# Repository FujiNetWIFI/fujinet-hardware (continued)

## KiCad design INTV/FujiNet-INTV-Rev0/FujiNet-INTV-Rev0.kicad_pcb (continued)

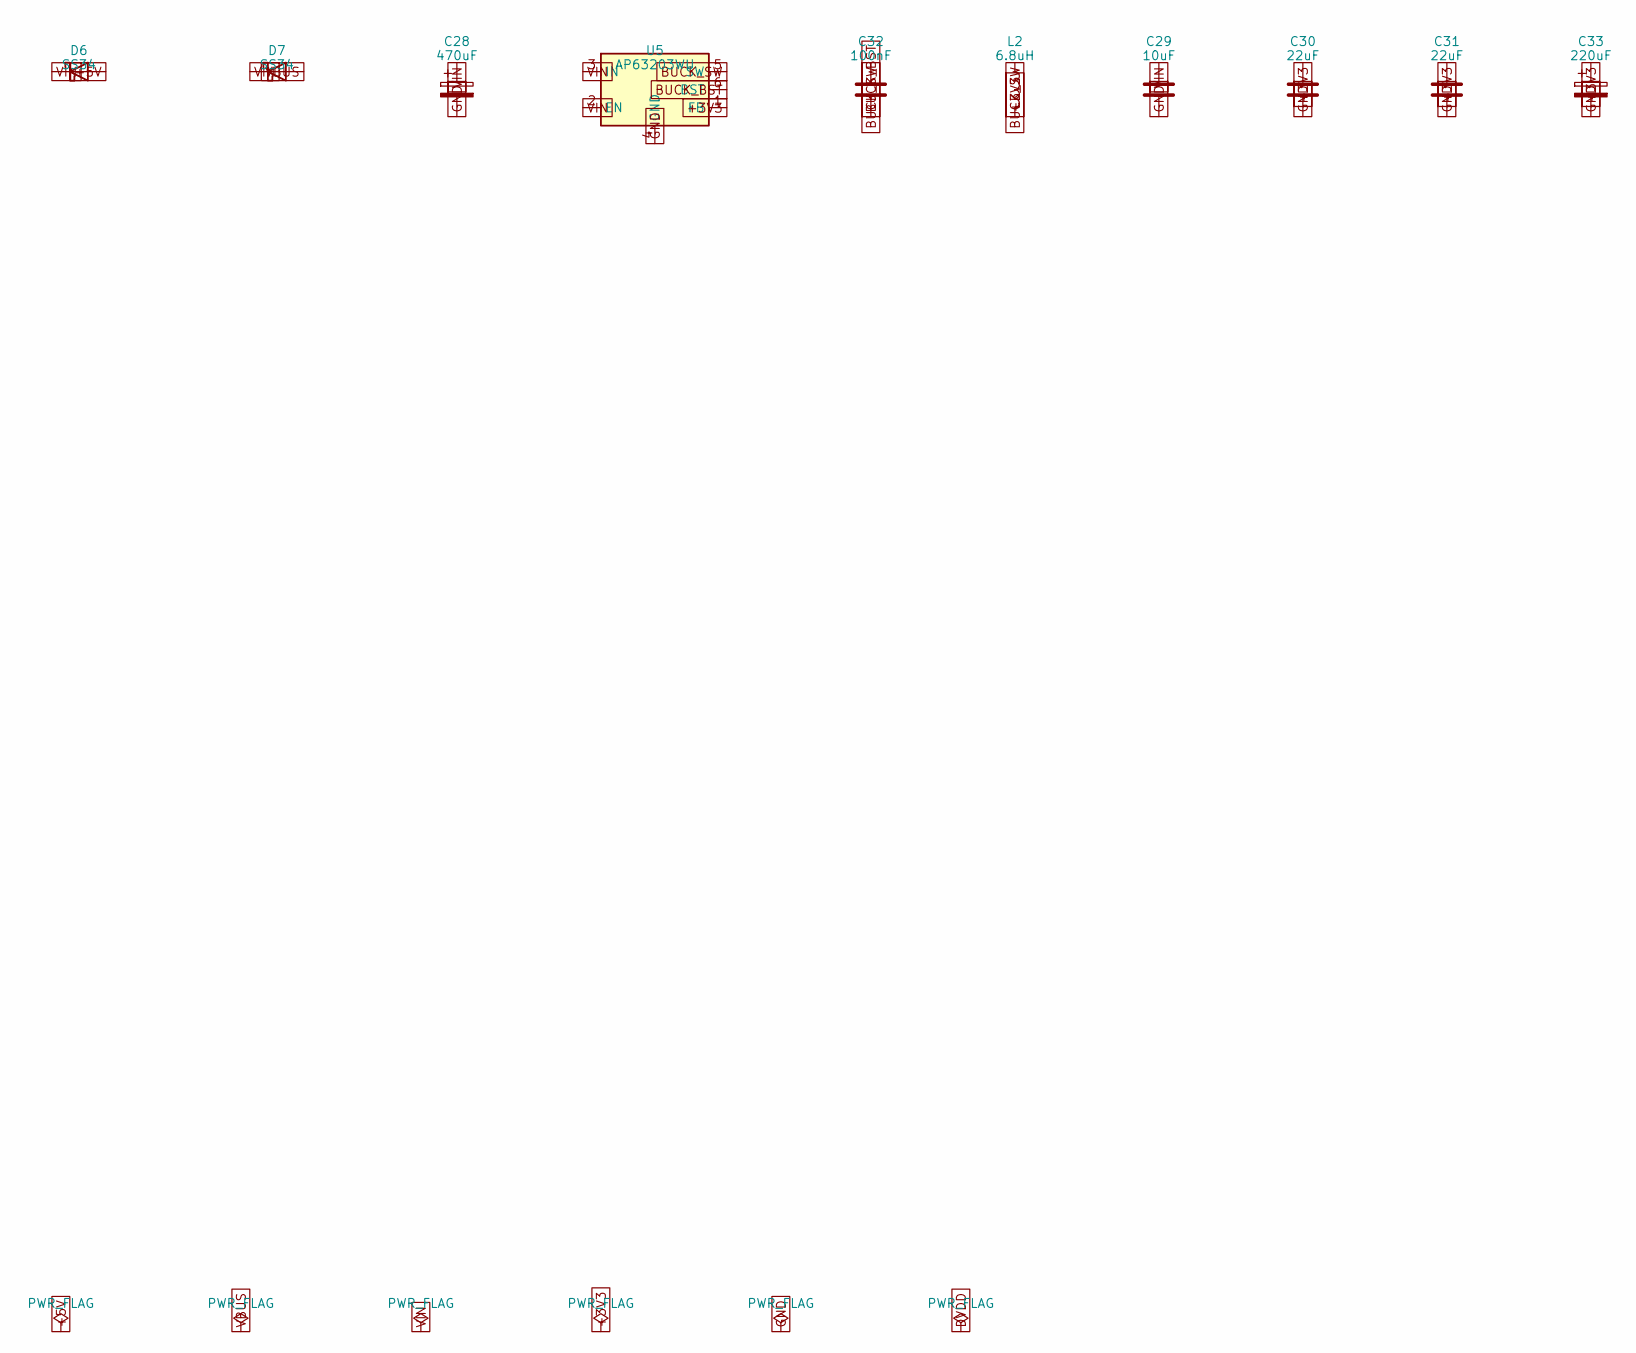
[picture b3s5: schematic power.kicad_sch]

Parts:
C28: 470uF; CP_EIA-7343-31_Kemet-D; MPN 6.3V polymer, 7343
C29: 10uF; C_0805_2012Metric
C30, C31: 22uF; C_0805_2012Metric; LCSC C45783
C32: 100nF; C_0603_1608Metric
C33: 220uF; CP_EIA-7343-31_Kemet-D; MPN 6.3V polymer, 7343
D6, D7: SS34; D_SMA; LCSC C8678
L2: 6.8uH; L_Sunlord_SWPA4030S; MPN 6.8uH >=2.5A shielded 4030
U5: AP63203WU; TSOT-23-6; MPN AP63203WU-7; LCSC C965680

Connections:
+3V3: C30.1, C31.1, C33.1, L2.2, U5.1 (FB); also elsewhere on the board
+5V: D6.2 (A); also elsewhere on the board
BUCK_BST: C32.2, U5.6 (BST)
BUCK_SW: C32.1, L2.1, U5.5 (SW)
GND: C28.2, C29.2, C30.2, C31.2, C33.2, U5.4 (GND); also elsewhere on the board
VBUS: D7.2 (A); also elsewhere on the board
VIN: C28.1, C29.1, D6.1 (K), D7.1 (K), U5.2 (EN), U5.3 (IN); also elsewhere on the board

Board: 4 copper layers, 84 parts (5 on the bottom side), 77 nets, no tracks yet.

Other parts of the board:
H1, H2: MountingHole_5.4mm_NPTH

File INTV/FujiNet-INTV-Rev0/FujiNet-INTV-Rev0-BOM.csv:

"Refs","Value","Footprint","MPN","LCSC","Description","DNP"
"C1,C2","15pF","FujiNet-INTV:C_0603_1608Metric","","","crystal load",""
"C3,C4,C5,C6,C7,C8,C9,C10,C11,C12,C19,C22,C23,C25,C26,C32","100nF","FujiNet-INTV:C_0603_1608Metric","","","IO0 debounce,SD VDD decoupling,U1 decoupling,U2 decoupling,U3 decoupling,WS2812 decoupling,bootstrap",""
"C13,C14,C15,C27","4.7uF","FujiNet-INTV:C_0603_1608Metric","","","DVDD bulk,U3 bulk,VREG_VIN bulk",""
"C16,C17,C20","10uF","FujiNet-INTV:C_0603_1608Metric","","C19702","3V3 bulk near U1,U2 bulk",""
"C18","1uF","FujiNet-INTV:C_0603_1608Metric","","","ECS audio filter (DNP)","DNP"
"C21,C24","1uF","FujiNet-INTV:C_0603_1608Metric","","","EN reset delay,U2 decoupling",""
"C28","470uF","FujiNet-INTV:CP_EIA-7343-31_Kemet-D","6.3V polymer, 7343","","VIN bulk",""
"C29","10uF","FujiNet-INTV:C_0805_2012Metric","","","buck input",""
"C30,C31","22uF","FujiNet-INTV:C_0805_2012Metric","","C45783","buck output",""
"C33","220uF","FujiNet-INTV:CP_EIA-7343-31_Kemet-D","6.3V polymer, 7343","","3V3 bulk (S3 WiFi bursts)",""
"D1","LED","FujiNet-INTV:LED_0603_1608Metric","","","RP activity LED (light pipe)",""
"D2","WS2812B-2020","FujiNet-INTV:LED_WS2812B-2020_PLCC4_2.0x2.0mm","WS2812B-2020","C5149201","status LED (fujiversal LED_STRIP, 1px)",""
"D3,D4,D5","ESD5Z5.0T1G","FujiNet-INTV:D_SOD-523","","C316061","ESD, USB D+,ESD, USB D-,ESD, VBUS",""
"D6,D7","SS34","FujiNet-INTV:D_SMA","","C8678","USB VBUS OR-ing,console 5V OR-ing / backfeed block",""
"J1","INTV_Cart_Edge_44","FujiNet-INTV:INTV_Cart_Edge_44","card edge, 2x22, 2.54mm","","Intellivision cartridge edge (geometry per PiNTY CARD)",""
"J2","microSD","FujiNet-INTV:microSD_SUNTECH_ST-TF-003A","SUNTECH ST-TF-003A","","push-push microSD (footprint per CoCo-FujiNet-Rev0000)",""
"J3","USB-C","FujiNet-INTV:USB_C_Receptacle_HRO_TYPE-C-31-M-12","HRO TYPE-C-31-M-12","C5178539","USB-C 16P (UART/flash port)",""
"L1","3.3uH","FujiNet-INTV:L_2016Metric","AOTA-B201610S3R3-101-T","C42411119","RP2354A core VREG inductor",""
"L2","6.8uH","FujiNet-INTV:L_Sunlord_SWPA4030S","6.8uH >=2.5A shielded 4030","","buck inductor (AP63203 datasheet)",""
"Q1,Q2,Q3","BC847","FujiNet-INTV:SOT-23","","C8598","BOOTSEL force (S3 GPIO5, Hi-Z idle),RUN force (S3 GPIO4, Hi-Z idle),console /RESET open-collector",""
"R1,R4,R8,R9,R10,R11","1k","FujiNet-INTV:R_0603_1608Metric","","","BOOTSEL series,LED series,Q1 base,Q2 base,Q3 base,XOUT series (RP2350 design guide)",""
"R2,R3","27R","FujiNet-INTV:R_0603_1608Metric","","","USB D+ series,USB D- series",""
"R5","1k","FujiNet-INTV:R_0603_1608Metric","","","ECS audio PWM series (DNP)","DNP"
"R6,R7,R13,R18","10k","FujiNet-INTV:R_0603_1608Metric","","","CP2102N /RST pull-up,EN pull-up,QSPI_SS/BOOTSEL pull-up,RUN pull-up",""
"R12","330R","FujiNet-INTV:R_0603_1608Metric","","","WS2812 data series",""
"R14,R15","5.1k","FujiNet-INTV:R_0603_1608Metric","","","CC1 pull-down (UFP),CC2 pull-down (UFP)",""
"R16","22.1k","FujiNet-INTV:R_0603_1608Metric","","","VBUS sense divider hi",""
"R17","47.5k","FujiNet-INTV:R_0603_1608Metric","","","VBUS sense divider lo",""
"RN1","4x10k","FujiNet-INTV:R_Array_Convex_4x0603","","","SD pull-ups",""
"SW1","RUN","FujiNet-INTV:SW_SPST_TL3342","","","RP2354A reset button",""
"SW2","BOOTSEL","FujiNet-INTV:SW_SPST_TL3342","","","RP2354A BOOTSEL button",""
"SW3","RESET","FujiNet-INTV:SW_SPST_TL3342","","","ESP32 reset button",""
"SW4","BOOT","FujiNet-INTV:SW_SPST_TL3342","","","ESP32 IO0 boot button",""
"U1","RP2354A","FujiNet-INTV:QFN-60-1EP_7x7mm_P0.4mm_EP3.4x3.4mm","RP2354A","C41378174","RP2350A + 2MB stacked QSPI flash, QFN-60",""
"U2","ESP32-S3-WROOM-1-N16R8","FujiNet-INTV:ESP32-S3-WROOM-1","ESP32-S3-WROOM-1-N16R8","C2913202","16MB QIO flash / 8MB octal PSRAM (IO35-37 NC)",""
"U3","CP2102N-A02-GQFN28","FujiNet-INTV:QFN-28-1EP_5x5mm_P0.5mm_EP3.35x3.35mm","CP2102N-A02-GQFN28R","","USB-UART bridge (DevKitC-1 UART port)",""
"U4","UMH3N","FujiNet-INTV:SOT-363_SC-70-6","","C123008","auto-program: DTR/RTS -> EN/IO0 (DevKitC-1 circuit)",""
"U5","AP63203WU","FujiNet-INTV:TSOT-23-6","AP63203WU-7","C965680","3.3V/2A sync buck (FB tied to VOUT: fixed 3.3V version)",""
"Y1","12MHz","FujiNet-INTV:Crystal_SMD_3225-4Pin_3.2x2.5mm","ABM8-272-T3","C20625731","12MHz 3225, CL=10pF (per PiNTY)",""

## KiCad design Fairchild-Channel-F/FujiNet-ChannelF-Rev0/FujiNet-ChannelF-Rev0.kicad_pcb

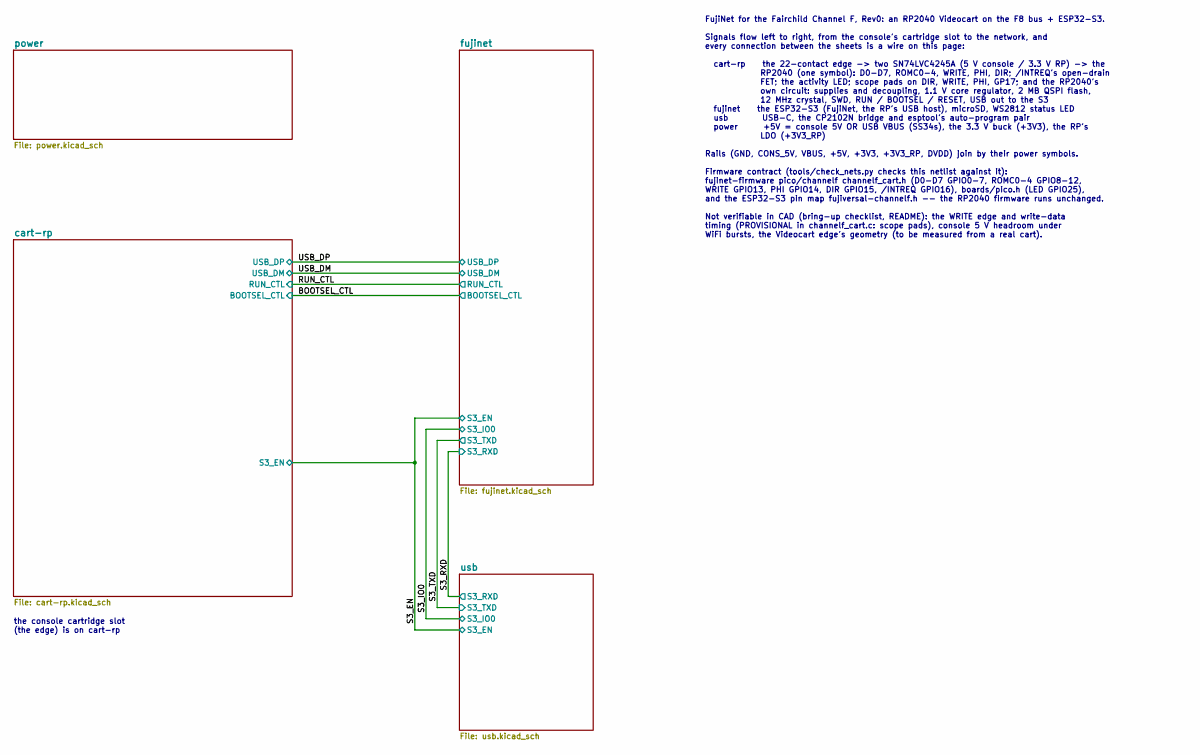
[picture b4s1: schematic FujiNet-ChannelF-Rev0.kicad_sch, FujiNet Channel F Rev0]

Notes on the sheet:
the console cartridge slot (the edge) is on cart-rp
FujiNet for the Fairchild Channel F, Rev0: an RP2040 Videocart on the F8 bus + ESP32-S3. Signals flow left to right, from the console's cartridge slot to the network, and every connection between the sheets is a wire on this page: cart-rp the 22-contact edge -> two SN74LVC4245A (5 V console / 3.3 V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

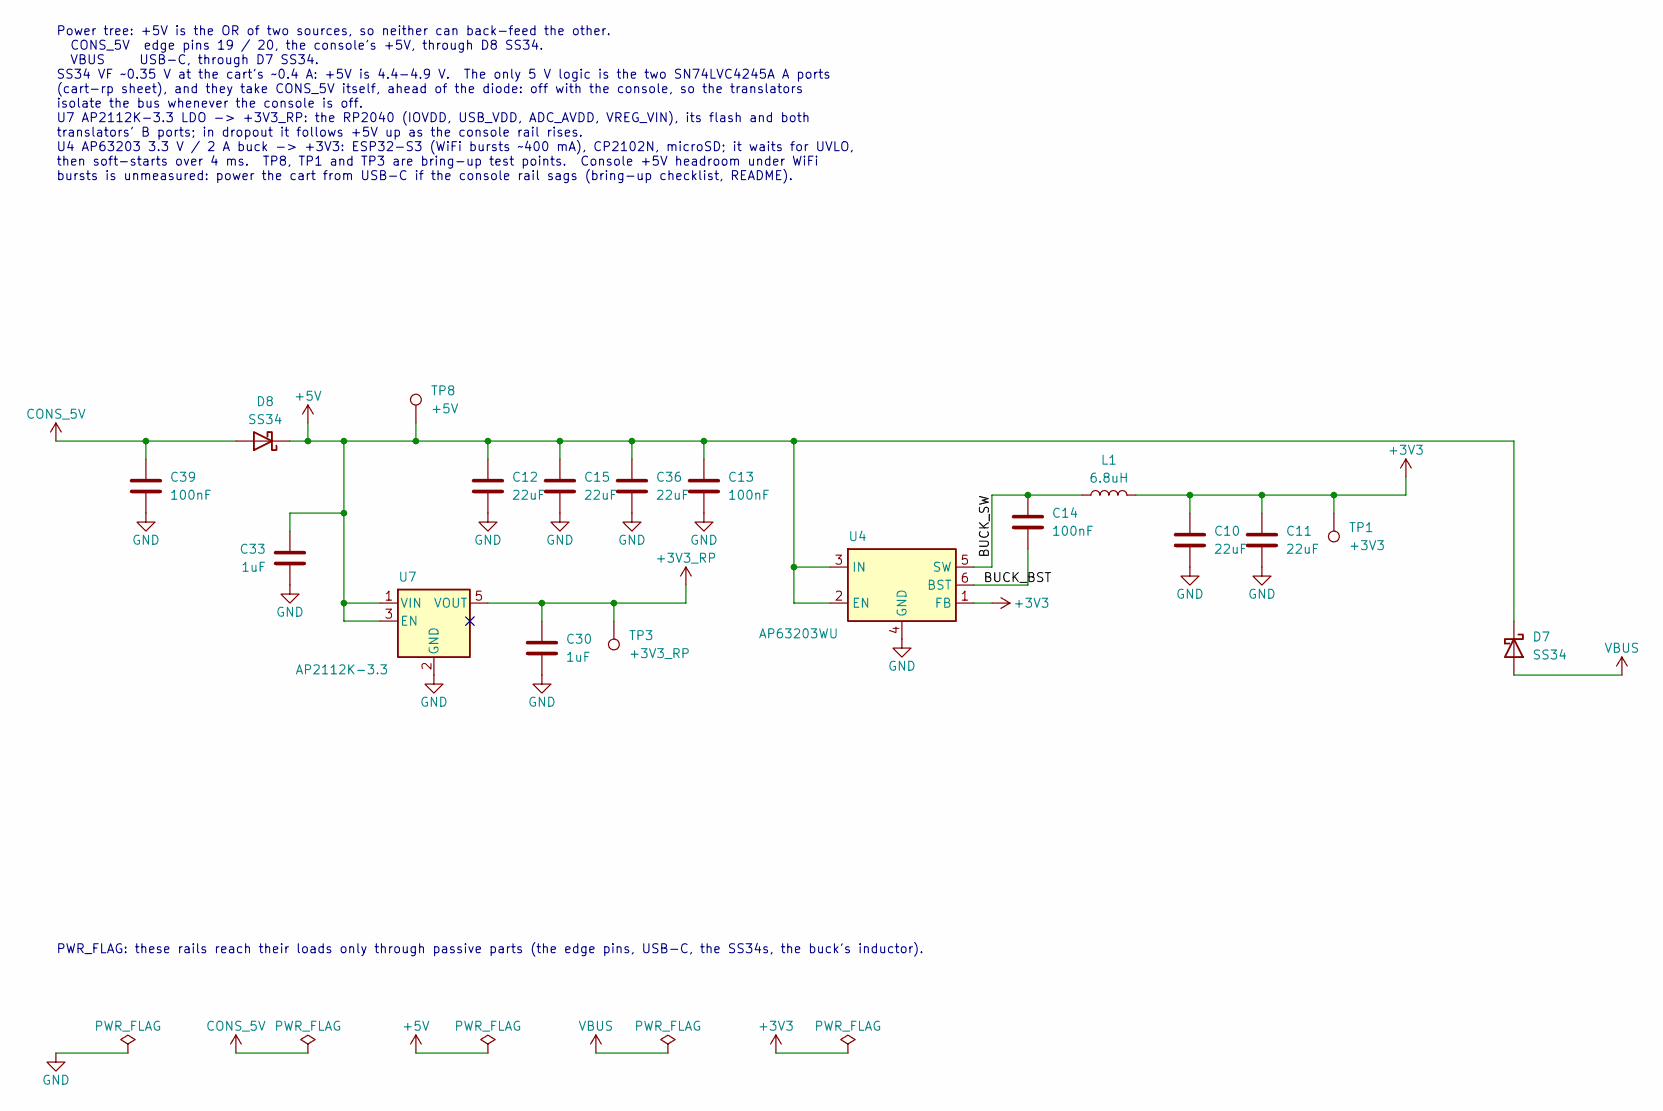
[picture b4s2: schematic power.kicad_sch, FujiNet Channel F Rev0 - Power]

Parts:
C10, C11, C12, C15, C36: 22uF; C_0805_2012Metric; MPN CL21A226MAQNNNE; LCSC C45783
C13, C14, C39: 100nF; C_0603_1608Metric; MPN CC0603KRX7R9BB104; LCSC C14663
C30, C33: 1uF; C_0603_1608Metric; MPN CL10A105KB8NNNC; LCSC C15849
D7, D8: SS34; D_SMA; MPN SS34; LCSC C8678
L1: 6.8uH; L_Sunlord_SWPA4030S; MPN SWPA4030S6R8MT; LCSC C62684
TP1: +3V3; TestPoint_Pad_D1.5mm
TP3: +3V3_RP; TestPoint_Pad_D1.5mm
TP8: +5V; TestPoint_Pad_D1.5mm
U4: AP63203WU; TSOT-23-6; MPN AP63203WU-7; LCSC C780769
U7: AP2112K-3.3; SOT-23-5; MPN AP2112K-3.3TRG1; LCSC C51118

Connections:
+3V3: C10.1, C11.1, L1.2, TP1.1, U4.1 (FB); also elsewhere on the board
+3V3_RP: C30.1, TP3.1, U7.5 (VOUT); also elsewhere on the board
+5V: C12.1, C13.1, C15.1, C33.1, C36.1, D7.1 (K), D8.1 (K), TP8.1, U4.2 (EN), U4.3 (IN), U7.1 (VIN), U7.3 (EN); also elsewhere on the board
/power/BUCK_BST: C14.2, U4.6 (BST)
/power/BUCK_SW: C14.1, L1.1, U4.5 (SW)
CONS_5V: C39.1, D8.2 (A); also elsewhere on the board
GND: C10.2, C11.2, C12.2, C13.2, C15.2, C30.2, C33.2, C36.2, C39.2, U4.4 (GND), U7.2 (GND); also elsewhere on the board
VBUS: D7.2 (A); also elsewhere on the board

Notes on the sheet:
PWR_FLAG: these rails reach their loads only through passive parts (the edge pins, USB-C, the SS34s, the buck's inductor).
Power tree: +5V is the OR of two sources, so neither can back-feed the other. CONS_5V edge pins 19 / 20, the console's +5V, through D8 SS34. VBUS USB-C, through D7 SS34. SS34 VF ~0.35 V at the cart's ~0.4 A: +5V is 4.4-4.9 V. The only 5 V logic is the two SN74LVC4245A A ports (cart-rp sheet), and t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

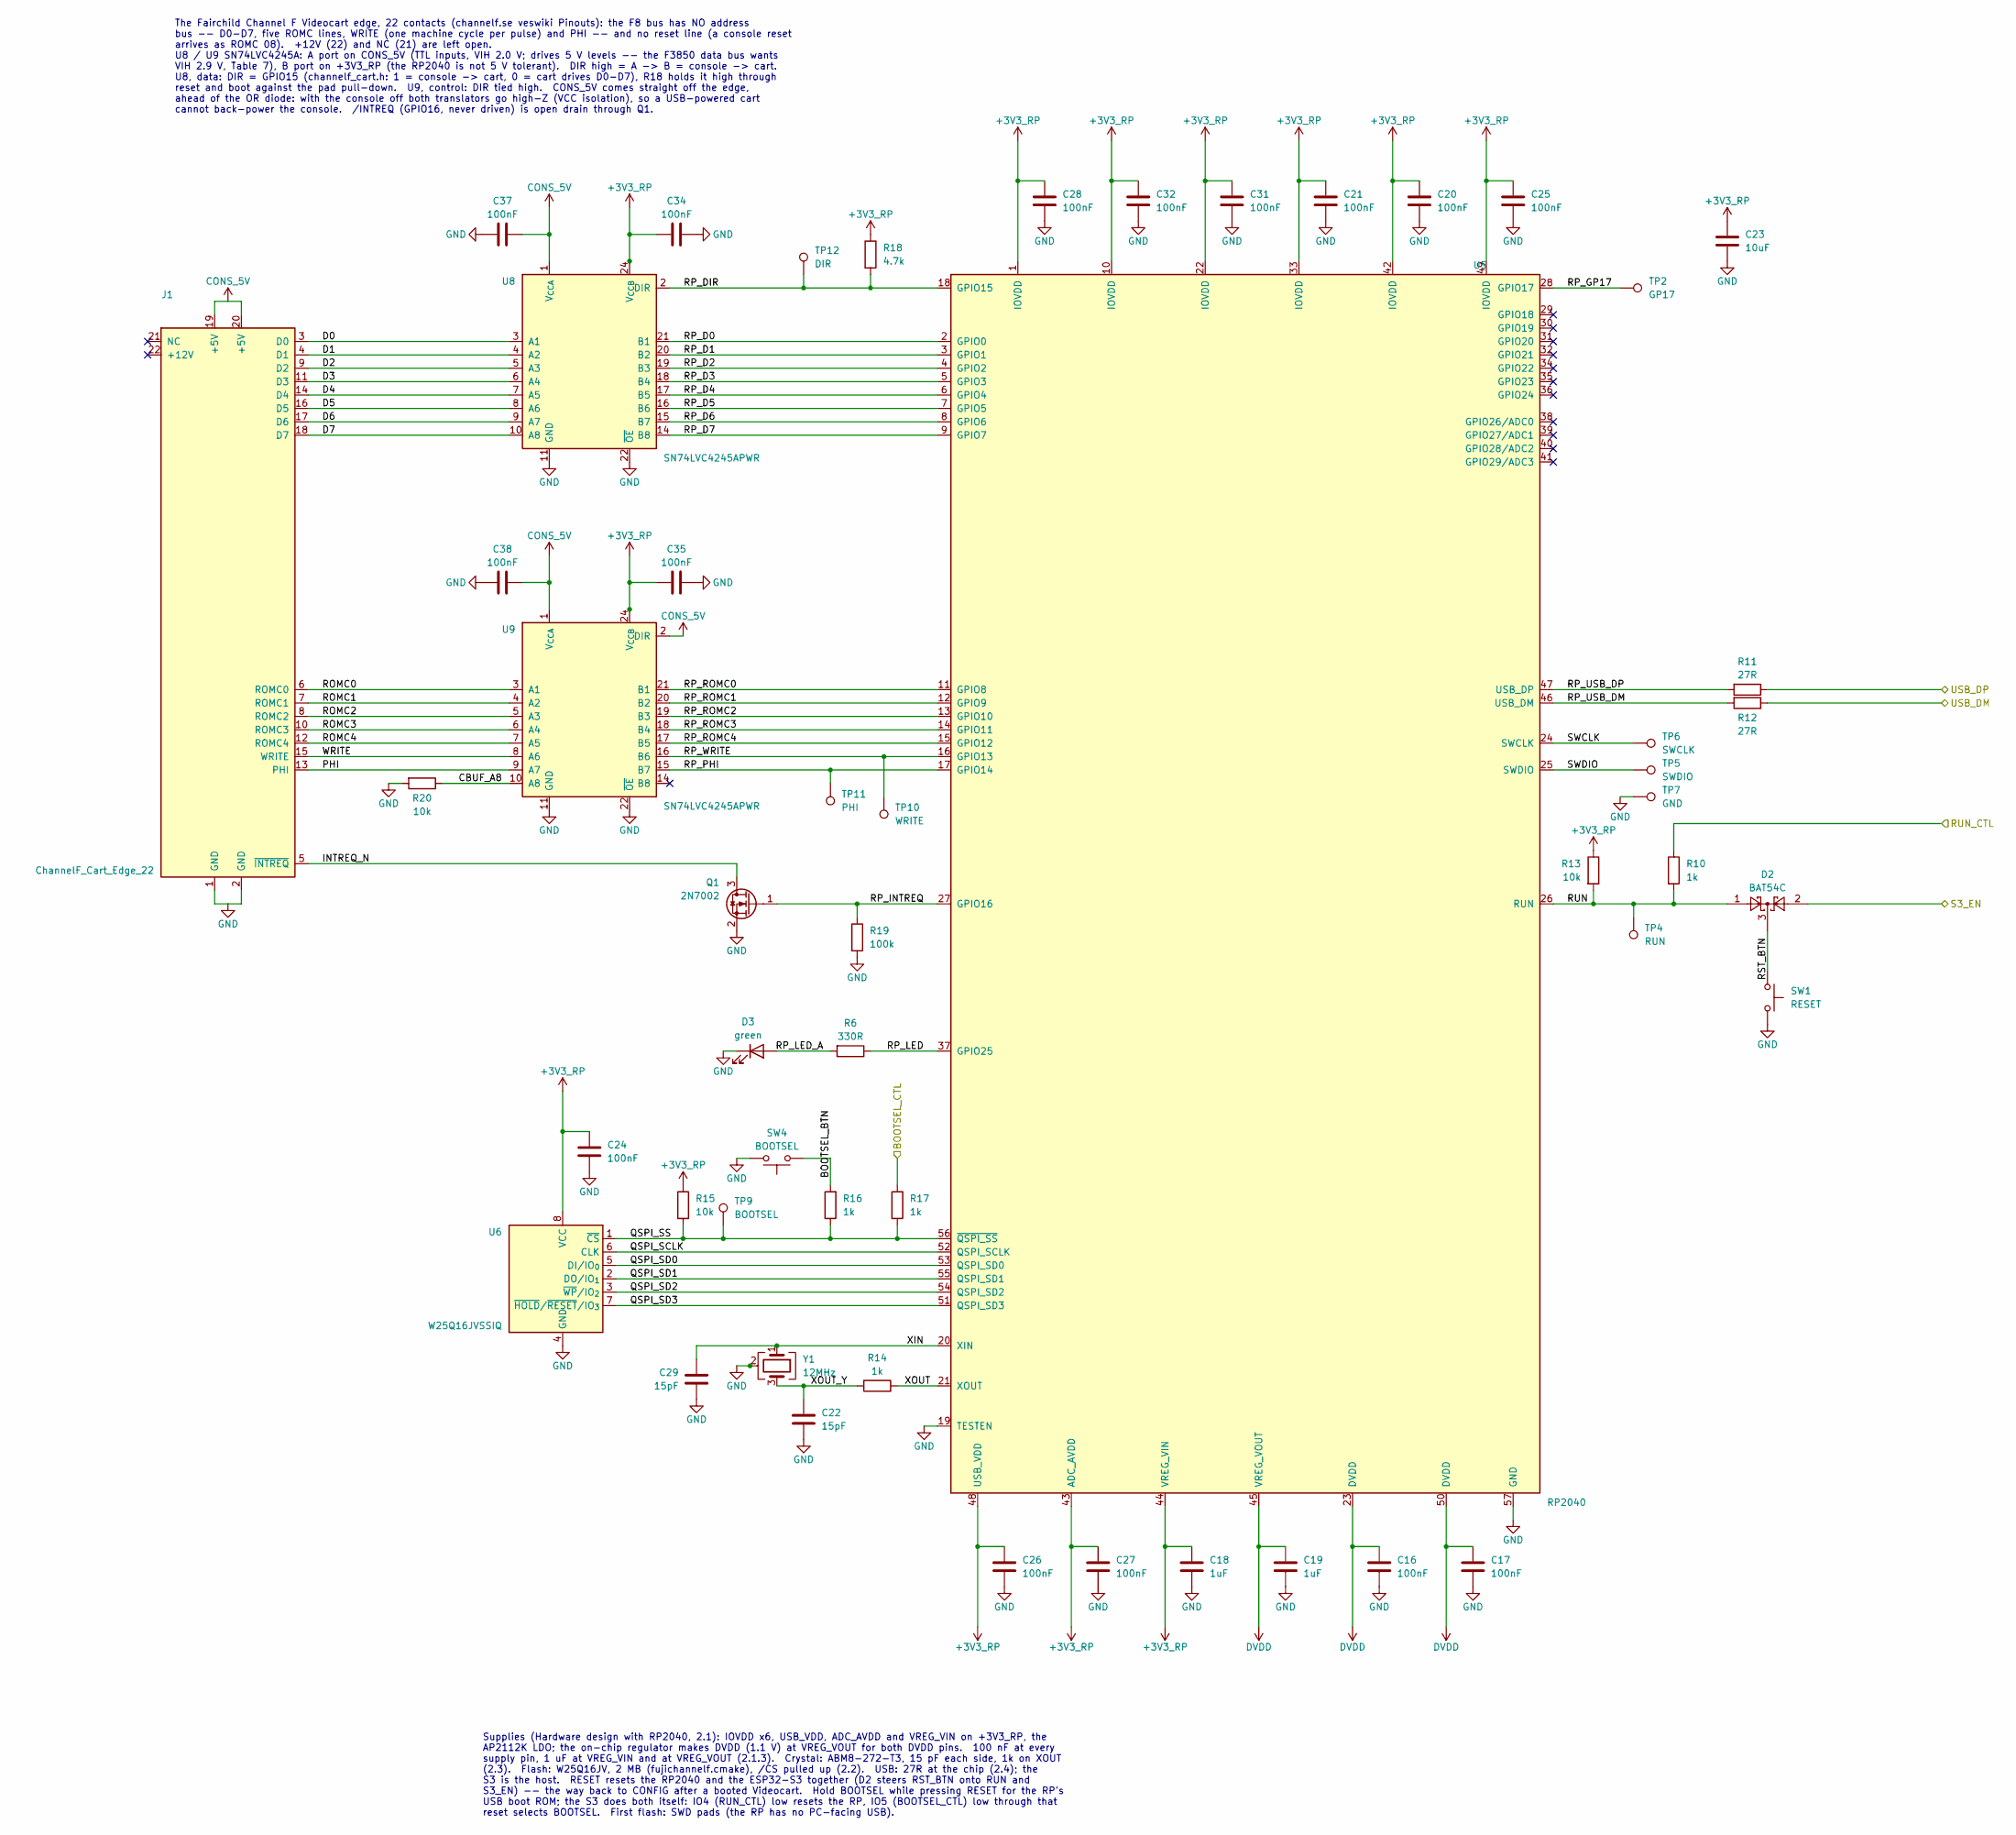
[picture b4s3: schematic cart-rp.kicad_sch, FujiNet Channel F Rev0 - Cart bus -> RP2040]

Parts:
C16, C17, C20, C21, C24, C25, C26, C27, C28, C31, C32, C34, C35, C37, C38: 100nF; C_0603_1608Metric; MPN CC0603KRX7R9BB104; LCSC C14663
C18, C19: 1uF; C_0603_1608Metric; MPN CL10A105KB8NNNC; LCSC C15849
C22, C29: 15pF; C_0603_1608Metric; MPN CL10C150JB8NNNC; LCSC C1644
C23: 10uF; C_0603_1608Metric; MPN CL10A106KP8NNNC; LCSC C19702
D2: BAT54C; SOT-23; MPN BAT54C,215; LCSC C37704
D3: green; LED_0603_1608Metric; MPN KT-0603G; LCSC C12624
J1: ChannelF_Cart_Edge_22; ChannelF_Videocart_Edge_22
Q1: 2N7002; SOT-23; MPN 2N7002; LCSC C8545
R6: 330R; R_0603_1608Metric; MPN 0603WAF3300T5E; LCSC C23138
R10, R14, R16, R17: 1k; R_0603_1608Metric; MPN 0603WAF1001T5E; LCSC C21190
R11, R12: 27R; R_0603_1608Metric; MPN 0603WAF270JT5E; LCSC C25190
R13, R15, R20: 10k; R_0603_1608Metric; MPN 0603WAF1002T5E; LCSC C25804
R18: 4.7k; R_0603_1608Metric; MPN 0603WAF4701T5E; LCSC C23162
R19: 100k; R_0603_1608Metric; MPN 0603WAF1003T5E; LCSC C25803
SW1: RESET; SW_SPST_TL3342; MPN TL3342F160QG; LCSC C2886898
SW4: BOOTSEL; SW_SPST_TL3342; MPN TL3342F160QG; LCSC C2886898
TP2: GP17; TestPoint_Pad_D1.5mm
TP4: RUN; TestPoint_Pad_D1.5mm
TP5: SWDIO; TestPoint_Pad_D1.5mm
TP6: SWCLK; TestPoint_Pad_D1.5mm
TP7: GND; TestPoint_Pad_D1.5mm
TP9: BOOTSEL; TestPoint_Pad_D1.5mm
TP10: WRITE; TestPoint_Pad_D1.5mm
TP11: PHI; TestPoint_Pad_D1.5mm
TP12: DIR; TestPoint_Pad_D1.5mm
U5: RP2040; QFN-56-1EP_7x7mm_P0.4mm_EP3.2x3.2mm; MPN RP2040; LCSC C2040
U6: W25Q16JVSSIQ; SOIC-8_5.3x5.3mm_P1.27mm; MPN W25Q16JVSSIQ; LCSC C82317
U8, U9: SN74LVC4245APWR; TSSOP-24_4.4x7.8mm_P0.65mm; MPN SN74LVC4245APWR; LCSC C7859
Y1: 12MHz; Crystal_SMD_3225-4Pin_3.2x2.5mm; MPN ABM8-272-T3; LCSC C20625731

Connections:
+3V3_RP: C18.1, C20.1, C21.1, C23.1, C24.1, C25.1, C26.1, C27.1, C28.1, C31.1, C32.1, C34.1, C35.1, R13.1, R15.1, R18.1, U5.1 (IOVDD), U5.10 (IOVDD), U5.22 (IOVDD), U5.33 (IOVDD), U5.42 (IOVDD), U5.43 (ADC_AVDD), U5.44 (VREG_VIN), U5.48 (USB_VDD), U5.49 (IOVDD), U6.8 (VCC), U8.23 (V_{CCB}), U8.24 (V_{CCB}), U9.23 (V_{CCB}), U9.24 (V_{CCB}); also elsewhere on the board
/BOOTSEL_CTL: R17.1; also elsewhere on the board
/RUN_CTL: R10.1; also elsewhere on the board
/S3_EN: D2.2; also elsewhere on the board
/USB_DM: R12.1; also elsewhere on the board
/USB_DP: R11.1; also elsewhere on the board
/cart-rp/BOOTSEL_BTN: R16.2, SW4.1
/cart-rp/CBUF_A8: R20.1, U9.10 (A8)
/cart-rp/D0: J1.3 (D0), U8.3 (A1)
/cart-rp/D1: J1.4 (D1), U8.4 (A2)
/cart-rp/D2: J1.9 (D2), U8.5 (A3)
/cart-rp/D3: J1.11 (D3), U8.6 (A4)
/cart-rp/D4: J1.14 (D4), U8.7 (A5)
/cart-rp/D5: J1.16 (D5), U8.8 (A6)
/cart-rp/D6: J1.17 (D6), U8.9 (A7)
/cart-rp/D7: J1.18 (D7), U8.10 (A8)
/cart-rp/INTREQ_N: J1.5 (~INTREQ), Q1.3 (D)
/cart-rp/PHI: J1.13 (PHI), U9.9 (A7)
/cart-rp/QSPI_SCLK: U5.52 (QSPI_SCLK), U6.6 (CLK)
/cart-rp/QSPI_SD0: U5.53 (QSPI_SD0), U6.5 (DI/IO_{0})
/cart-rp/QSPI_SD1: U5.55 (QSPI_SD1), U6.2 (DO/IO_{1})
/cart-rp/QSPI_SD2: U5.54 (QSPI_SD2), U6.3 (~WP/IO_{2})
/cart-rp/QSPI_SD3: U5.51 (QSPI_SD3), U6.7 (~HOLD/~RESET/IO_{3})
/cart-rp/QSPI_SS: R15.2, R16.1, R17.2, TP9.1, U5.56 (~QSPI_SS), U6.1 (~CS)
/cart-rp/ROMC0: J1.6 (ROMC0), U9.3 (A1)
/cart-rp/ROMC1: J1.7 (ROMC1), U9.4 (A2)
/cart-rp/ROMC2: J1.8 (ROMC2), U9.5 (A3)
/cart-rp/ROMC3: J1.10 (ROMC3), U9.6 (A4)
/cart-rp/ROMC4: J1.12 (ROMC4), U9.7 (A5)
/cart-rp/RP_D0: U5.2 (GPIO0), U8.21 (B1)
/cart-rp/RP_D1: U5.3 (GPIO1), U8.20 (B2)
/cart-rp/RP_D2: U5.4 (GPIO2), U8.19 (B3)
/cart-rp/RP_D3: U5.5 (GPIO3), U8.18 (B4)
/cart-rp/RP_D4: U5.6 (GPIO4), U8.17 (B5)
/cart-rp/RP_D5: U5.7 (GPIO5), U8.16 (B6)
/cart-rp/RP_D6: U5.8 (GPIO6), U8.15 (B7)
/cart-rp/RP_D7: U5.9 (GPIO7), U8.14 (B8)
/cart-rp/RP_DIR: R18.2, TP12.1, U5.18 (GPIO15), U8.2 (DIR)
/cart-rp/RP_GP17: TP2.1, U5.28 (GPIO17)
/cart-rp/RP_INTREQ: Q1.1 (G), R19.1, U5.27 (GPIO16)
/cart-rp/RP_LED: R6.1, U5.37 (GPIO25)
/cart-rp/RP_LED_A: D3.2 (A), R6.2
/cart-rp/RP_PHI: TP11.1, U5.17 (GPIO14), U9.15 (B7)
/cart-rp/RP_ROMC0: U5.11 (GPIO8), U9.21 (B1)
/cart-rp/RP_ROMC1: U5.12 (GPIO9), U9.20 (B2)
/cart-rp/RP_ROMC2: U5.13 (GPIO10), U9.19 (B3)
/cart-rp/RP_ROMC3: U5.14 (GPIO11), U9.18 (B4)
/cart-rp/RP_ROMC4: U5.15 (GPIO12), U9.17 (B5)
/cart-rp/RP_USB_DM: R12.2, U5.46 (USB_DM)
/cart-rp/RP_USB_DP: R11.2, U5.47 (USB_DP)
/cart-rp/RP_WRITE: TP10.1, U5.16 (GPIO13), U9.16 (B6)
/cart-rp/RST_BTN: D2.3, SW1.1
/cart-rp/RUN: D2.1, R10.2, R13.2, TP4.1, U5.26 (RUN)
/cart-rp/SWCLK: TP6.1, U5.24 (SWCLK)
/cart-rp/SWDIO: TP5.1, U5.25 (SWDIO)
/cart-rp/WRITE: J1.15 (WRITE), U9.8 (A6)
/cart-rp/XIN: C29.1, U5.20 (XIN), Y1.1
/cart-rp/XOUT: R14.1, U5.21 (XOUT)
/cart-rp/XOUT_Y: C22.1, R14.2, Y1.3
CONS_5V: C37.1, C38.1, J1.19 (+5V), J1.20 (+5V), U8.1 (V_{CCA}), U9.1 (V_{CCA}), U9.2 (DIR); also elsewhere on the board
DVDD: C16.1, C17.1, C19.1, U5.23 (DVDD), U5.45 (VREG_VOUT), U5.50 (DVDD)
GND: C16.2, C17.2, C18.2, C19.2, C20.2, C21.2, C22.2, C23.2, C24.2, C25.2, C26.2, C27.2, C28.2, C29.2, C31.2, C32.2, C34.2, C35.2, C37.2, C38.2, D3.1 (K), J1.1 (GND), J1.2 (GND), Q1.2 (S), R19.2, R20.2, SW1.2, SW4.2, TP7.1, U5.19 (TESTEN), U5.57 (GND), U6.4 (GND), U8.11 (GND), U8.12 (GND), U8.13 (GND), U8.22 (~OE), U9.11 (GND), U9.12 (GND), U9.13 (GND), U9.22 (~OE), Y1.2 (G), Y1.4 (G); also elsewhere on the board

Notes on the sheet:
The Fairchild Channel F Videocart edge, 22 contacts (channelf.se veswiki Pinouts): the F8 bus has NO address bus -- D0-D7, five ROMC lines, WRITE (one machine cycle per pulse) and PHI -- and no reset line (a console reset arrives as ROMC 08). +12V (22) and NC (21) are left open. U8 / U9 SN74LVC4245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
Supplies (Hardware design with RP2040, 2.1): IOVDD x6, USB_VDD, ADC_AVDD and VREG_VIN on +3V3_RP, the AP2112K LDO; the on-chip regulator makes DVDD (1.1 V) at VREG_VOUT for both DVDD pins. 100 nF at every supply pin, 1 uF at VREG_VIN and at VREG_VOUT (2.1.3). Crystal: ABM8-272-T3, 15 pF each side, 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

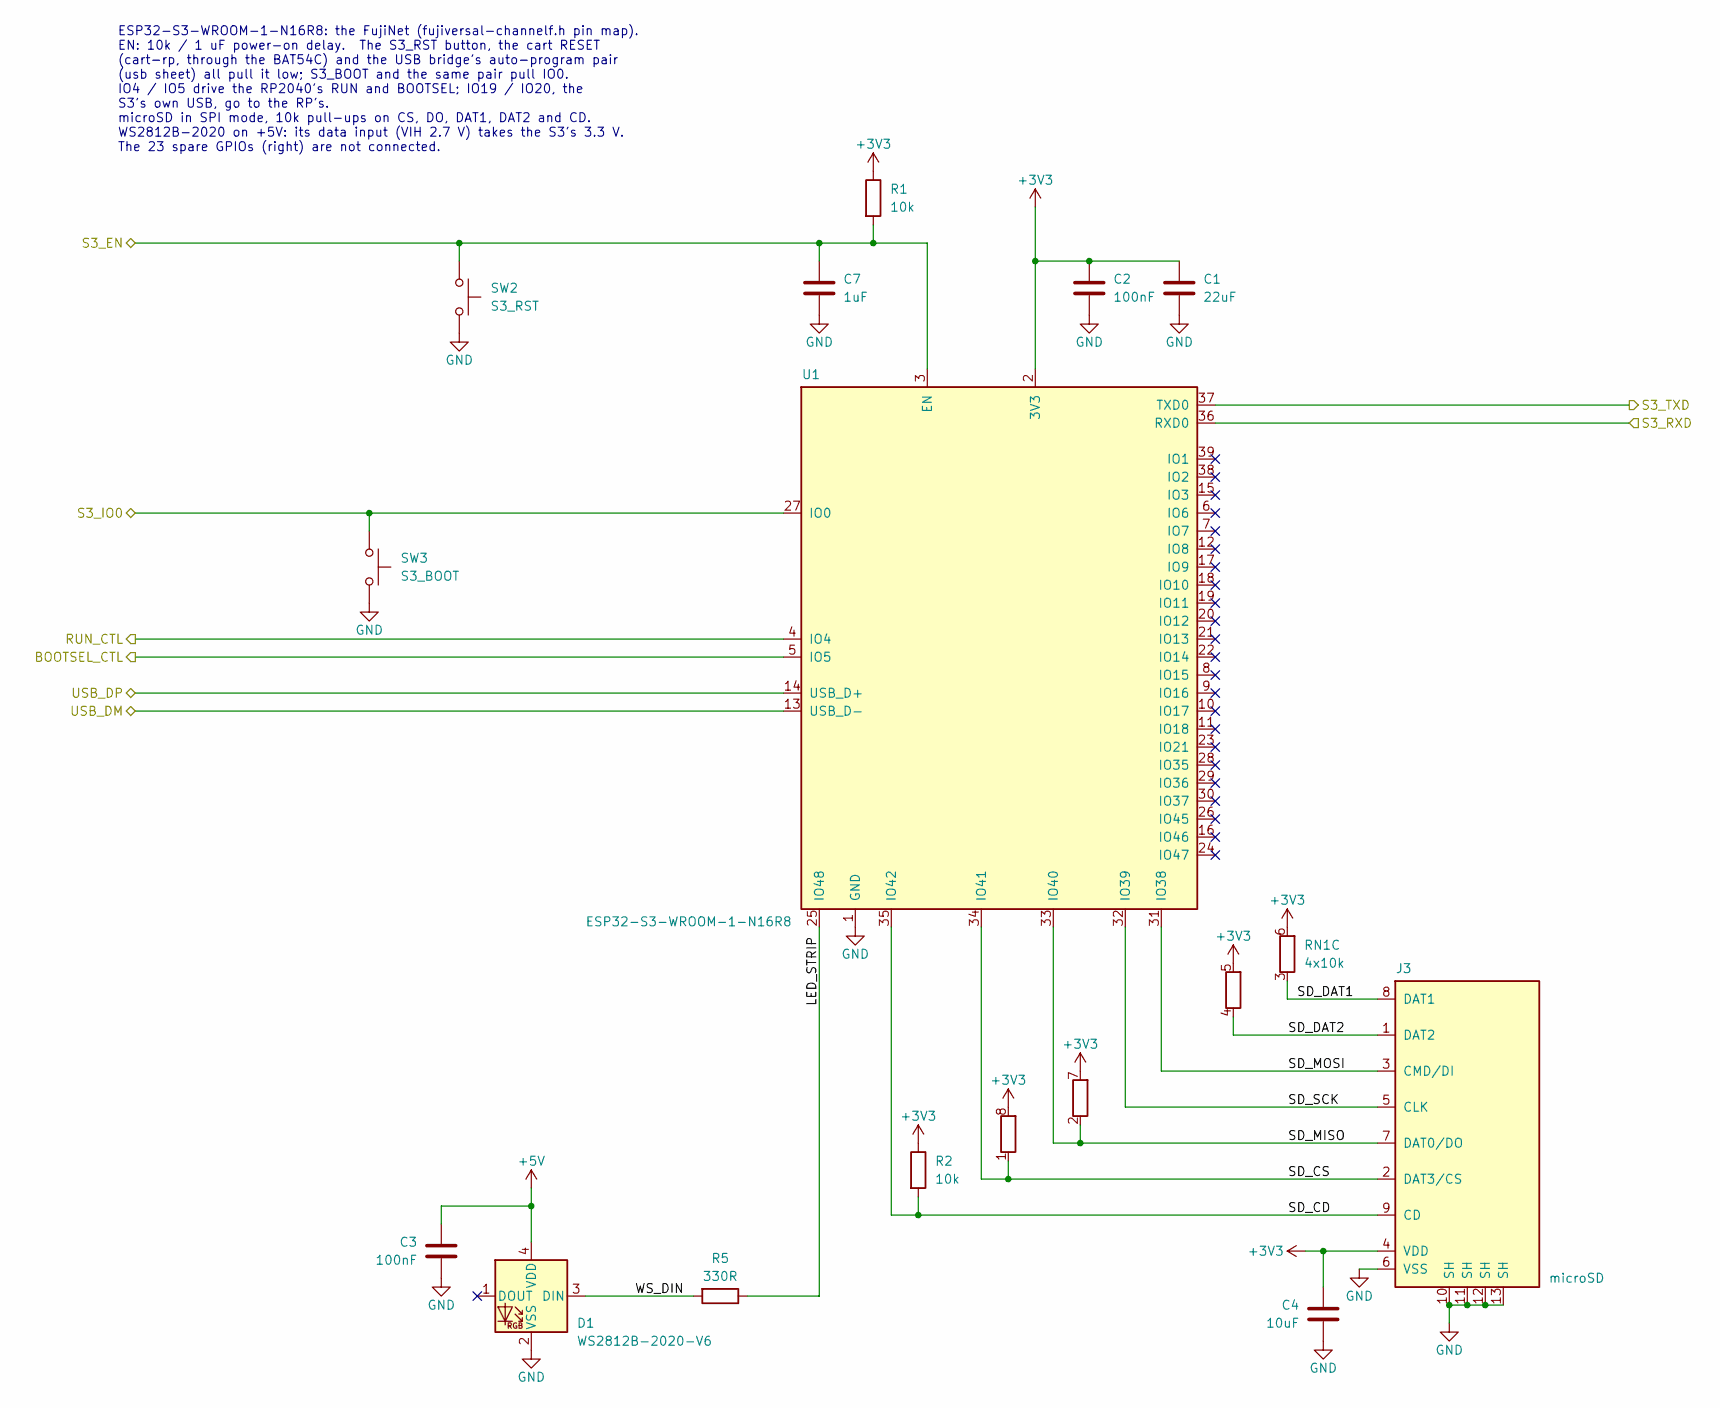
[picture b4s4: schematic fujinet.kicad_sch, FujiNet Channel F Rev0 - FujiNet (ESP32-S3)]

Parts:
C1: 22uF; C_0805_2012Metric; MPN CL21A226MAQNNNE; LCSC C45783
C2, C3: 100nF; C_0603_1608Metric; MPN CC0603KRX7R9BB104; LCSC C14663
C4: 10uF; C_0603_1608Metric; MPN CL10A106KP8NNNC; LCSC C19702
C7: 1uF; C_0603_1608Metric; MPN CL10A105KB8NNNC; LCSC C15849
D1: WS2812B-2020-V6; LED_WS2812B-2020_PLCC4_2.0x2.0mm; MPN WS2812B-2020-V6; LCSC C52917434
J3: microSD; TF-SMD_TF-015; MPN TF-015; LCSC C113206
R1, R2: 10k; R_0603_1608Metric; MPN 0603WAF1002T5E; LCSC C25804
R5: 330R; R_0603_1608Metric; MPN 0603WAF3300T5E; LCSC C23138
RN1: 4x10k; R_Array_Convex_4x0603; MPN 4D03WGJ0103T5E; LCSC C29718
SW2: S3_RST; SW_SPST_TL3342; MPN TL3342F160QG; LCSC C2886898
SW3: S3_BOOT; SW_SPST_TL3342; MPN TL3342F160QG; LCSC C2886898
U1: ESP32-S3-WROOM-1-N16R8; ESP32-S3-WROOM-1; MPN ESP32-S3-WROOM-1-N16R8; LCSC C2913202

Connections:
+3V3: C1.1, C2.1, C4.1, J3.4 (VDD), R1.1, R2.1, RN1.5 (R4.2), RN1.6 (R3.2), RN1.7 (R2.2), RN1.8 (R1.2), U1.2 (3V3); also elsewhere on the board
+5V: C3.1, D1.4 (VDD); also elsewhere on the board
/BOOTSEL_CTL: U1.5 (IO5); also elsewhere on the board
/RUN_CTL: U1.4 (IO4); also elsewhere on the board
/S3_EN: C7.1, R1.2, SW2.1, U1.3 (EN); also elsewhere on the board
/S3_IO0: SW3.1, U1.27 (IO0); also elsewhere on the board
/S3_RXD: U1.36 (RXD0); also elsewhere on the board
/S3_TXD: U1.37 (TXD0); also elsewhere on the board
/USB_DM: U1.13 (USB_D-); also elsewhere on the board
/USB_DP: U1.14 (USB_D+); also elsewhere on the board
/fujinet/LED_STRIP: R5.1, U1.25 (IO48)
/fujinet/SD_CD: J3.9 (CD), R2.2, U1.35 (IO42)
/fujinet/SD_CS: J3.2 (DAT3/CS), RN1.1 (R1.1), U1.34 (IO41)
/fujinet/SD_DAT1: J3.8 (DAT1), RN1.3 (R3.1)
/fujinet/SD_DAT2: J3.1 (DAT2), RN1.4 (R4.1)
/fujinet/SD_MISO: J3.7 (DAT0/DO), RN1.2 (R2.1), U1.33 (IO40)
/fujinet/SD_MOSI: J3.3 (CMD/DI), U1.31 (IO38)
/fujinet/SD_SCK: J3.5 (CLK), U1.32 (IO39)
/fujinet/WS_DIN: D1.3 (DIN), R5.2
GND: C1.2, C2.2, C3.2, C4.2, C7.2, D1.2 (VSS), J3.6 (VSS), J3.10 (SH), J3.11 (SH), J3.12 (SH), J3.13 (SH), SW2.2, SW3.2, U1.1 (GND), U1.40 (GND), U1.41 (GND); also elsewhere on the board

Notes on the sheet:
ESP32-S3-WROOM-1-N16R8: the FujiNet (fujiversal-channelf.h pin map). EN: 10k / 1 uF power-on delay. The S3_RST button, the cart RESET (cart-rp, through the BAT54C) and the USB bridge's auto-program pair (usb sheet) all pull it low; S3_BOOT and the same pair pull IO0. IO4 / IO5 drive the RP2040's RU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

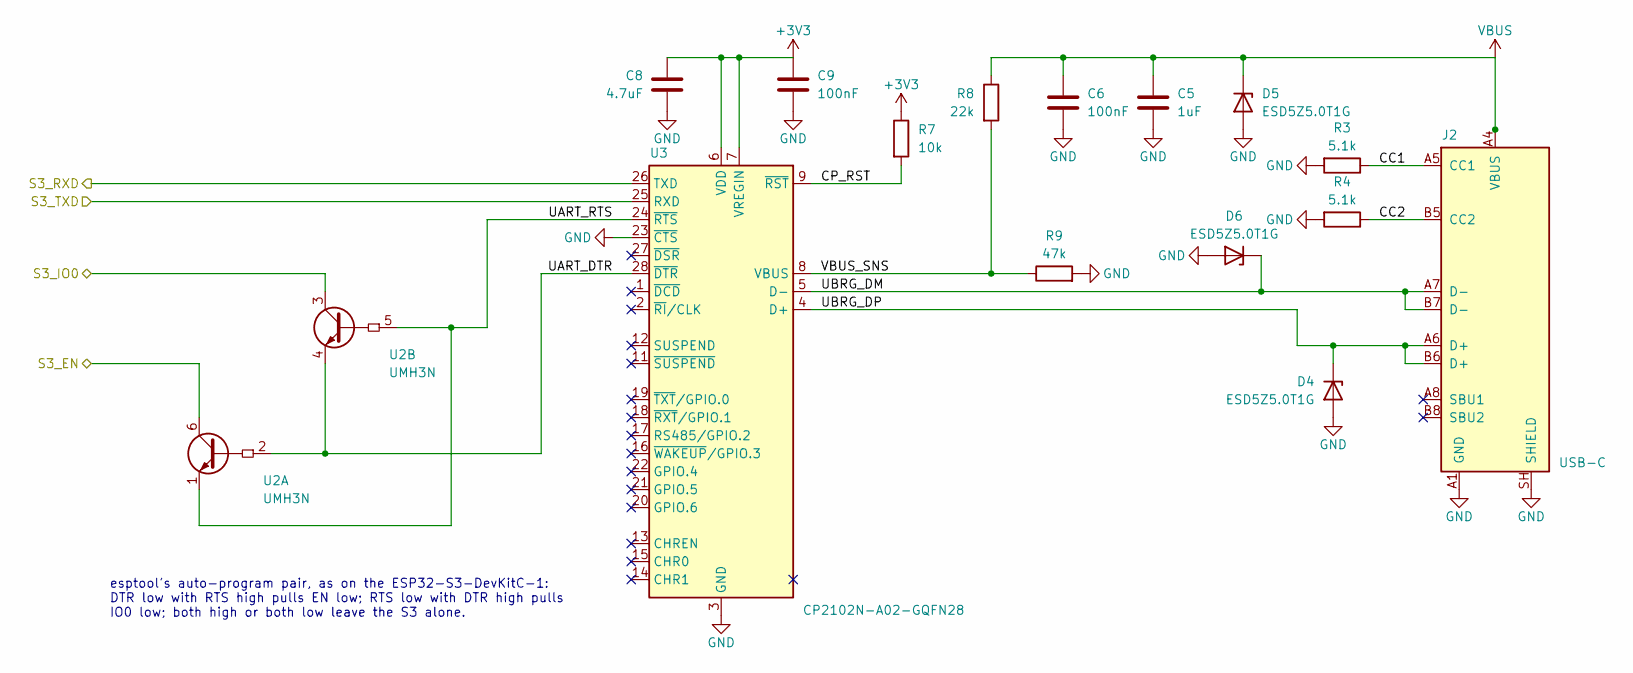
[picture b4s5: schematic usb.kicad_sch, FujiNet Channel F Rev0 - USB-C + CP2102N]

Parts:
C5: 1uF; C_0603_1608Metric; MPN CL10A105KB8NNNC; LCSC C15849
C6, C9: 100nF; C_0603_1608Metric; MPN CC0603KRX7R9BB104; LCSC C14663
C8: 4.7uF; C_0603_1608Metric; MPN CL10A475KO8NNNC; LCSC C19666
D4, D5, D6: ESD5Z5.0T1G; D_SOD-523; MPN ESD5Z5.0T1G; LCSC C82044
J2: USB-C; USB_C_Receptacle_HRO_TYPE-C-31-M-12; MPN TYPE-C-31-M-12; LCSC C165948
R3, R4: 5.1k; R_0603_1608Metric; MPN 0603WAF5101T5E; LCSC C23186
R7: 10k; R_0603_1608Metric; MPN 0603WAF1002T5E; LCSC C25804
R8: 22k; R_0603_1608Metric; MPN 0603WAF2202T5E; LCSC C31850
R9: 47k; R_0603_1608Metric; MPN 0603WAF4702T5E; LCSC C25819
U2: UMH3N; SOT-363_SC-70-6; MPN UMH3N; LCSC C62892
U3: CP2102N-A02-GQFN28; QFN-28-1EP_5x5mm_P0.5mm_EP3.35x3.35mm; MPN CP2102N-A02-GQFN28R; LCSC C964632

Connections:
+3V3: C8.1, C9.1, R7.1, U3.6 (VDD), U3.7 (VREGIN); also elsewhere on the board
/S3_EN: U2.6 (C1); also elsewhere on the board
/S3_IO0: U2.3 (C2); also elsewhere on the board
/S3_RXD: U3.26 (TXD); also elsewhere on the board
/S3_TXD: U3.25 (RXD); also elsewhere on the board
/usb/CC1: J2.A5 (CC1), R3.1
/usb/CC2: J2.B5 (CC2), R4.1
/usb/CP_RST: R7.2, U3.9 (~RST)
/usb/UART_DTR: U2.2 (B1), U2.4 (E2), U3.28 (~DTR)
/usb/UART_RTS: U2.1 (E1), U2.5 (B2), U3.24 (~RTS)
/usb/UBRG_DM: D6.1 (K), J2.A7 (D-), J2.B7 (D-), U3.5 (D-)
/usb/UBRG_DP: D4.1 (K), J2.A6 (D+), J2.B6 (D+), U3.4 (D+)
/usb/VBUS_SNS: R8.2, R9.1, U3.8 (VBUS)
GND: C5.2, C6.2, C8.2, C9.2, D4.2 (A), D5.2 (A), D6.2 (A), J2.A1 (GND), J2.A12 (GND), J2.B1 (GND), J2.B12 (GND), J2.SH (SHIELD), R3.2, R4.2, R9.2, U3.3 (GND), U3.23 (~CTS), U3.29 (GND); also elsewhere on the board
VBUS: C5.1, C6.1, D5.1 (K), J2.A4 (VBUS), J2.A9 (VBUS), J2.B4 (VBUS), J2.B9 (VBUS), R8.1; also elsewhere on the board

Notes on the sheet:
esptool's auto-program pair, as on the ESP32-S3-DevKitC-1: DTR low with RTS high pulls EN low; RTS low with DTR high pulls IO0 low; both high or both low leave the S3 alone.
